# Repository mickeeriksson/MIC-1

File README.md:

# MIC-1
This is the repo for MIC-1

## Contents
- kernels/ : contains the MONITOR ROM source for MIC-1

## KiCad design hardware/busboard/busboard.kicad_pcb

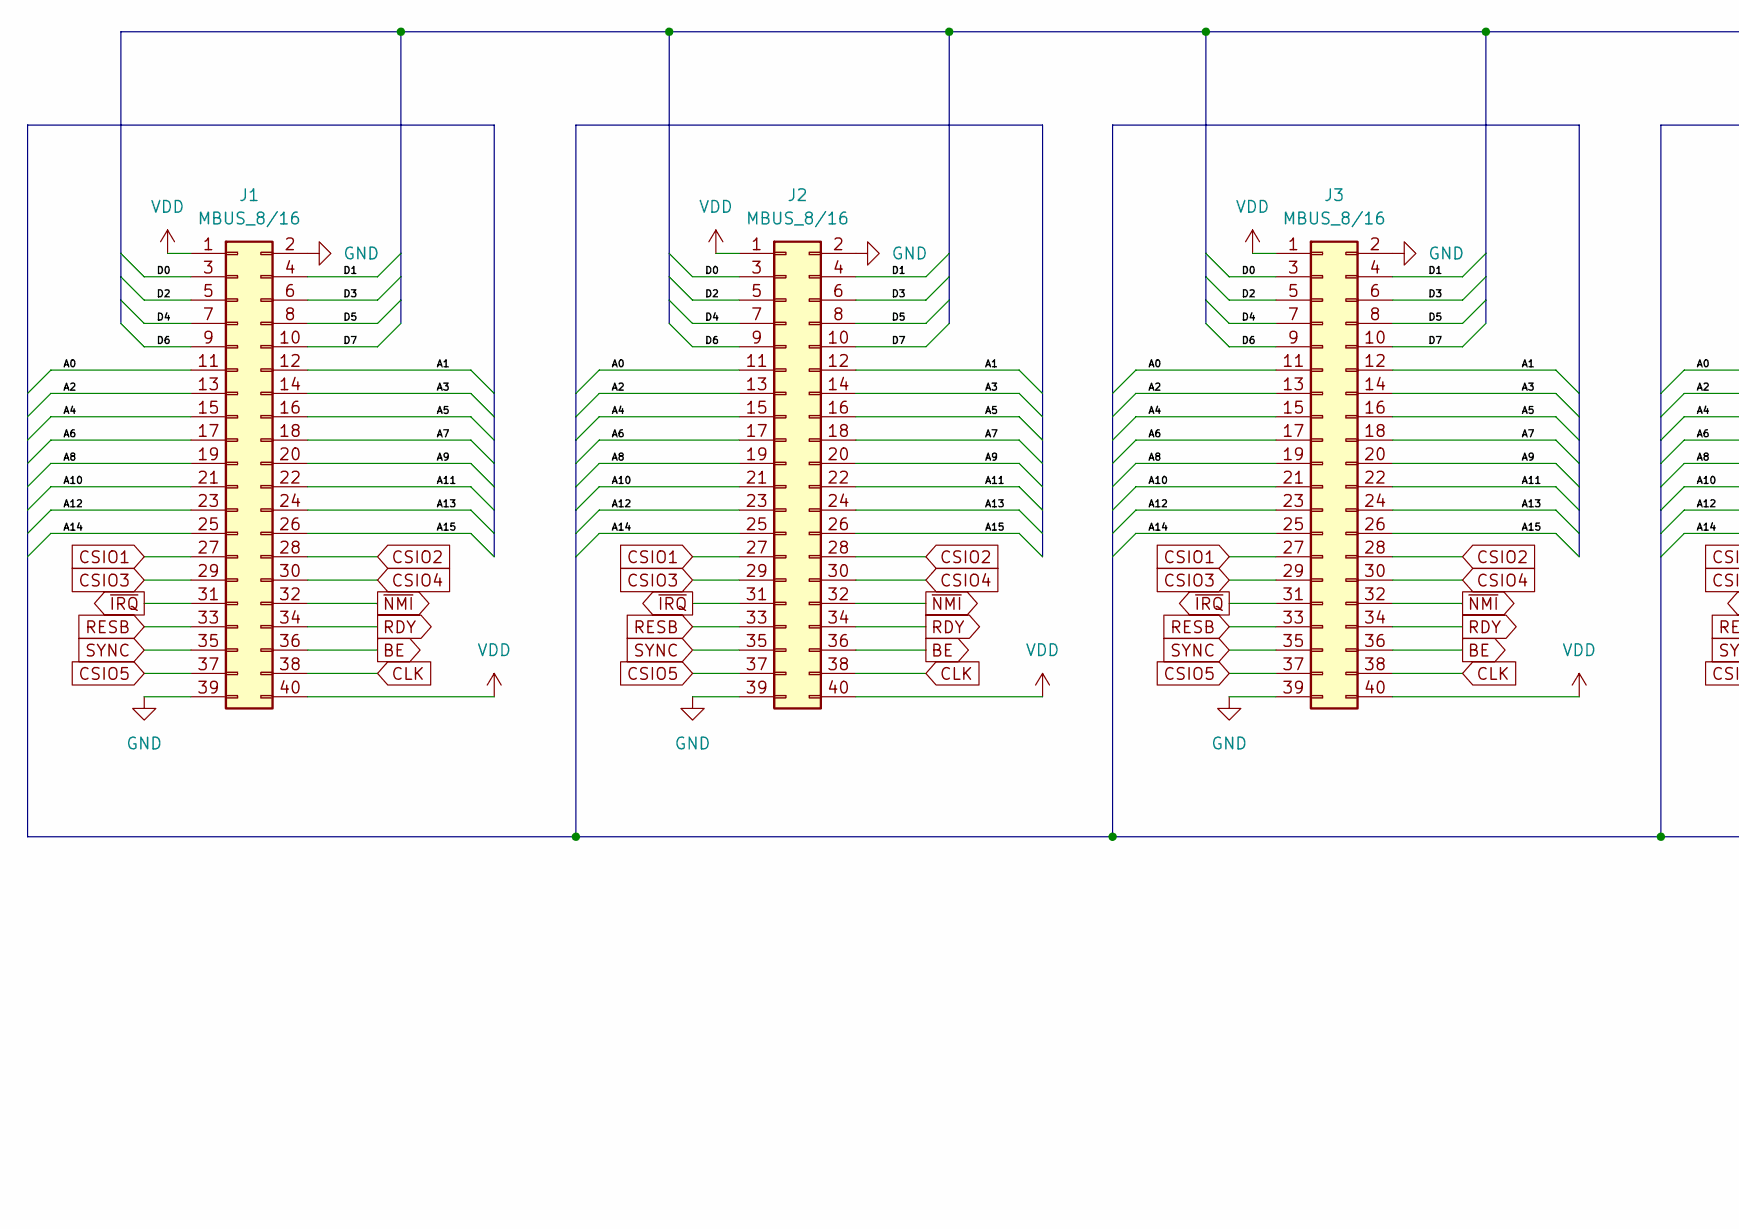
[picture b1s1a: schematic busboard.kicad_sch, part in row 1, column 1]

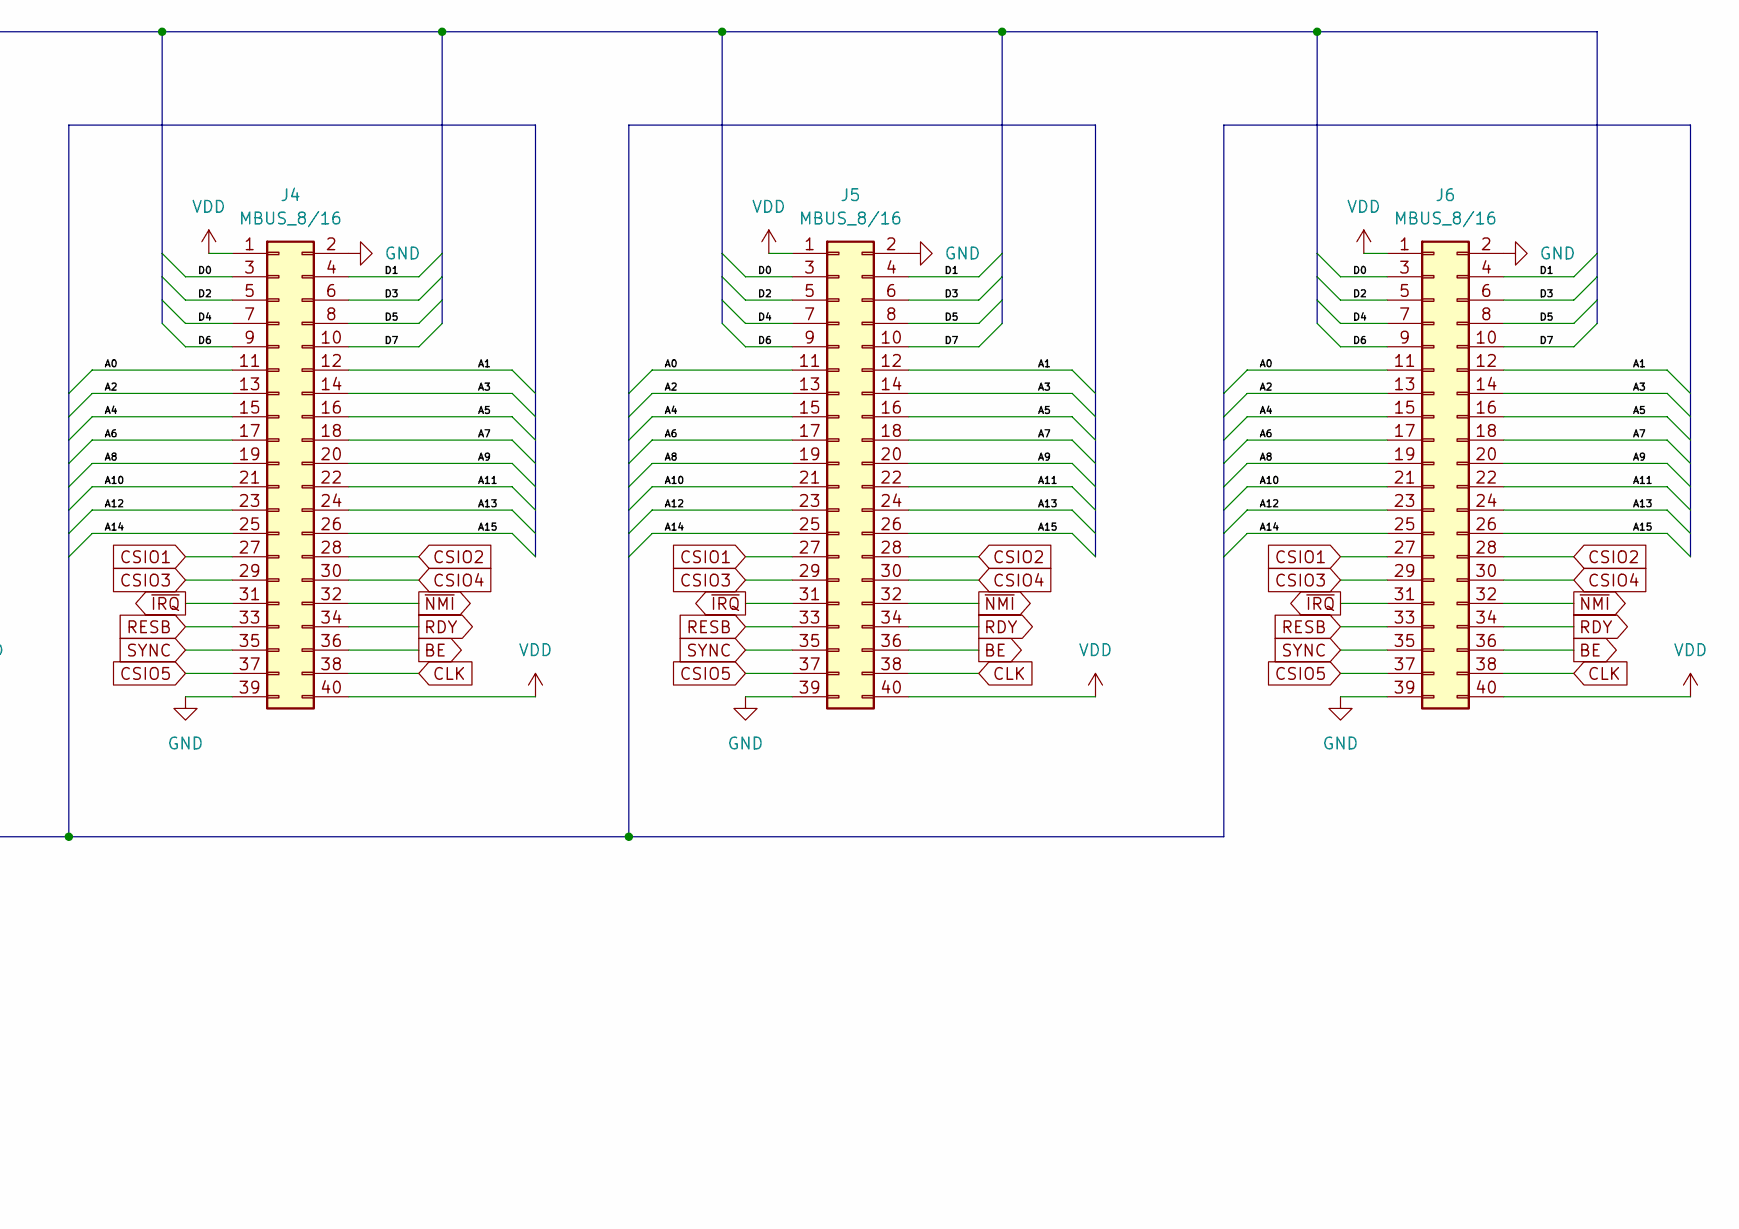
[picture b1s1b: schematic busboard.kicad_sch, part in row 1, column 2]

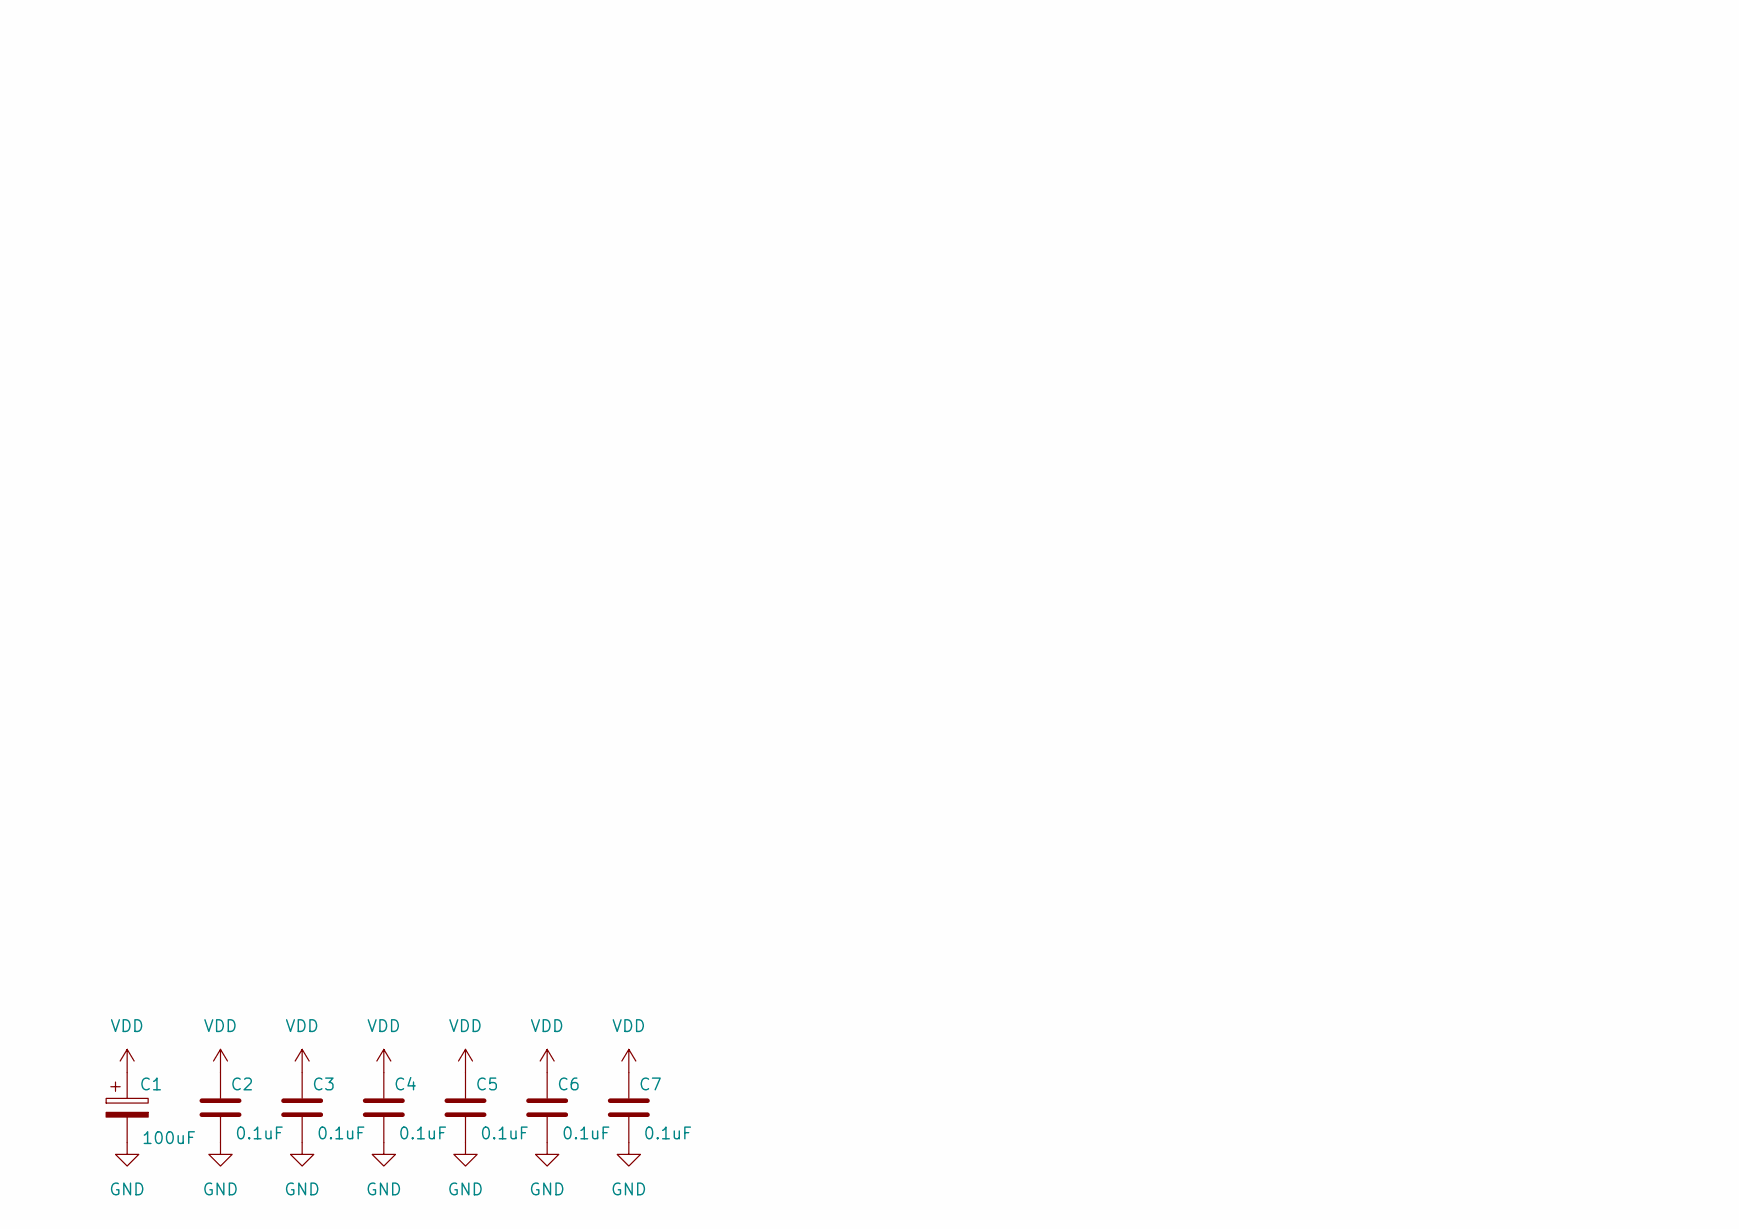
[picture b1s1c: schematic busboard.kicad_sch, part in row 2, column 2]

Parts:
C1: 100uF; CP_Radial_D5.0mm_P2.50mm
C2, C3, C4, C5, C6, C7: 0.1uF; C_Disc_D3.0mm_W2.0mm_P2.50mm
J1, J2, J3, J4, J5, J6: MBUS_8/16; PinHeader_2x20_P2.54mm_Vertical

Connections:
/A0: J1.11, J2.11, J3.11, J4.11, J5.11, J6.11
/A1: J1.12, J2.12, J3.12, J4.12, J5.12, J6.12
/A2: J1.13, J2.13, J3.13, J4.13, J5.13, J6.13
/A3: J1.14, J2.14, J3.14, J4.14, J5.14, J6.14
/A4: J1.15, J2.15, J3.15, J4.15, J5.15, J6.15
/A5: J1.16, J2.16, J3.16, J4.16, J5.16, J6.16
/A6: J1.17, J2.17, J3.17, J4.17, J5.17, J6.17
/A7: J1.18, J2.18, J3.18, J4.18, J5.18, J6.18
/A8: J1.19, J2.19, J3.19, J4.19, J5.19, J6.19
/A9: J1.20, J2.20, J3.20, J4.20, J5.20, J6.20
/A10: J1.21, J2.21, J3.21, J4.21, J5.21, J6.21
/A11: J1.22, J2.22, J3.22, J4.22, J5.22, J6.22
/A12: J1.23, J2.23, J3.23, J4.23, J5.23, J6.23
/A13: J1.24, J2.24, J3.24, J4.24, J5.24, J6.24
/A14: J1.25, J2.25, J3.25, J4.25, J5.25, J6.25
/A15: J1.26, J2.26, J3.26, J4.26, J5.26, J6.26
/D0: J1.3, J2.3, J3.3, J4.3, J5.3, J6.3
/D1: J1.4, J2.4, J3.4, J4.4, J5.4, J6.4
/D2: J1.5, J2.5, J3.5, J4.5, J5.5, J6.5
/D3: J1.6, J2.6, J3.6, J4.6, J5.6, J6.6
/D4: J1.7, J2.7, J3.7, J4.7, J5.7, J6.7
/D5: J1.8, J2.8, J3.8, J4.8, J5.8, J6.8
/D6: J1.9, J2.9, J3.9, J4.9, J5.9, J6.9
/D7: J1.10, J2.10, J3.10, J4.10, J5.10, J6.10
BE: J1.36, J2.36, J3.36, J4.36, J5.36, J6.36
CLK: J1.38, J2.38, J3.38, J4.38, J5.38, J6.38
CSIO1: J1.27, J2.27, J3.27, J4.27, J5.27, J6.27
CSIO2: J1.28, J2.28, J3.28, J4.28, J5.28, J6.28
CSIO3: J1.29, J2.29, J3.29, J4.29, J5.29, J6.29
CSIO4: J1.30, J2.30, J3.30, J4.30, J5.30, J6.30
CSIO5: J1.37, J2.37, J3.37, J4.37, J5.37, J6.37
GND: C1.2, C2.2, C3.2, C4.2, C5.2, C6.2, C7.2, J1.2, J1.39, J2.2, J2.39, J3.2, J3.39, J4.2, J4.39, J5.2, J5.39, J6.2, J6.39
RDY: J1.34, J2.34, J3.34, J4.34, J5.34, J6.34
RESB: J1.33, J2.33, J3.33, J4.33, J5.33, J6.33
SYNC: J1.35, J2.35, J3.35, J4.35, J5.35, J6.35
VDD: C1.1, C2.1, C3.1, C4.1, C5.1, C6.1, C7.1, J1.1, J1.40, J2.1, J2.40, J3.1, J3.40, J4.1, J4.40, J5.1, J5.40, J6.1, J6.40
~IRQ: J1.31, J2.31, J3.31, J4.31, J5.31, J6.31
~NMI: J1.32, J2.32, J3.32, J4.32, J5.32, J6.32

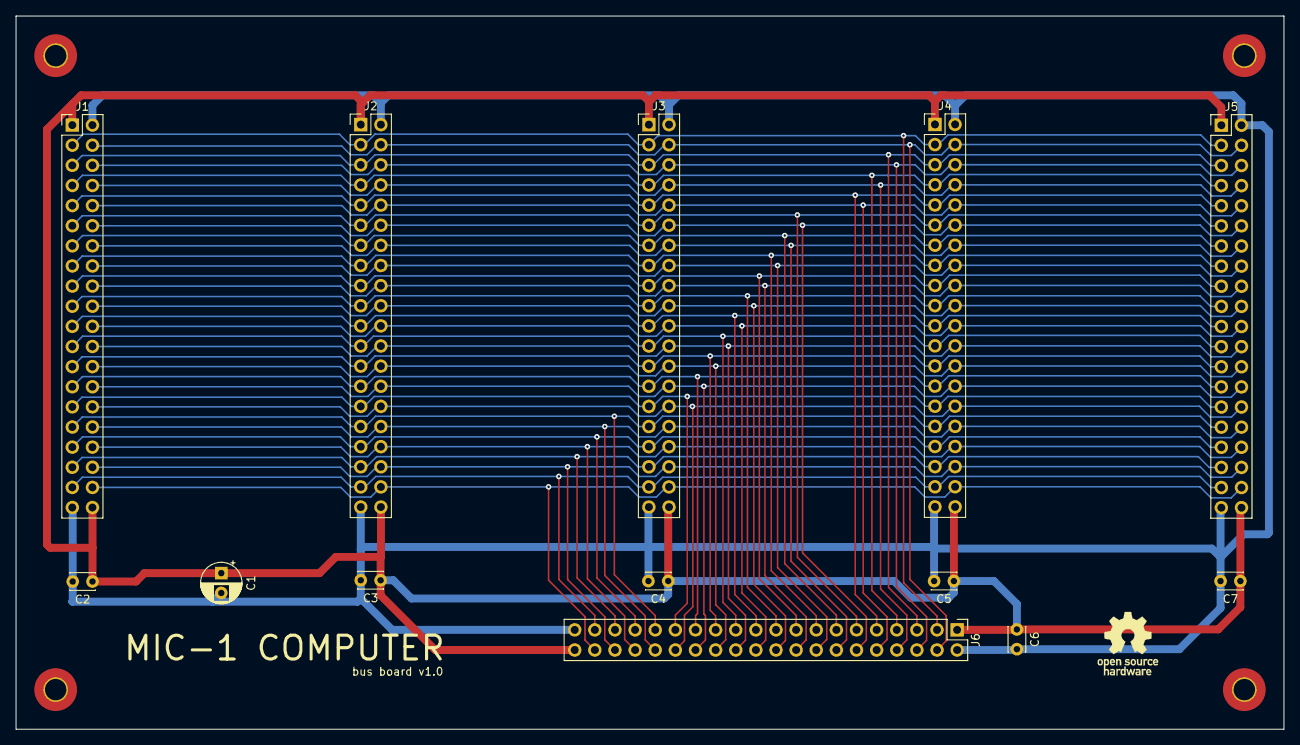
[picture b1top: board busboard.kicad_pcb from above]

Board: 2 copper layers, 160.0 x 90.0 mm, 17 parts (0 on the bottom side), 38 nets.

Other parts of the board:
hole1, hole1#2, hole1#3, hole1#4: MountingHole_2.7mm_M2.5_Pad_TopBottom

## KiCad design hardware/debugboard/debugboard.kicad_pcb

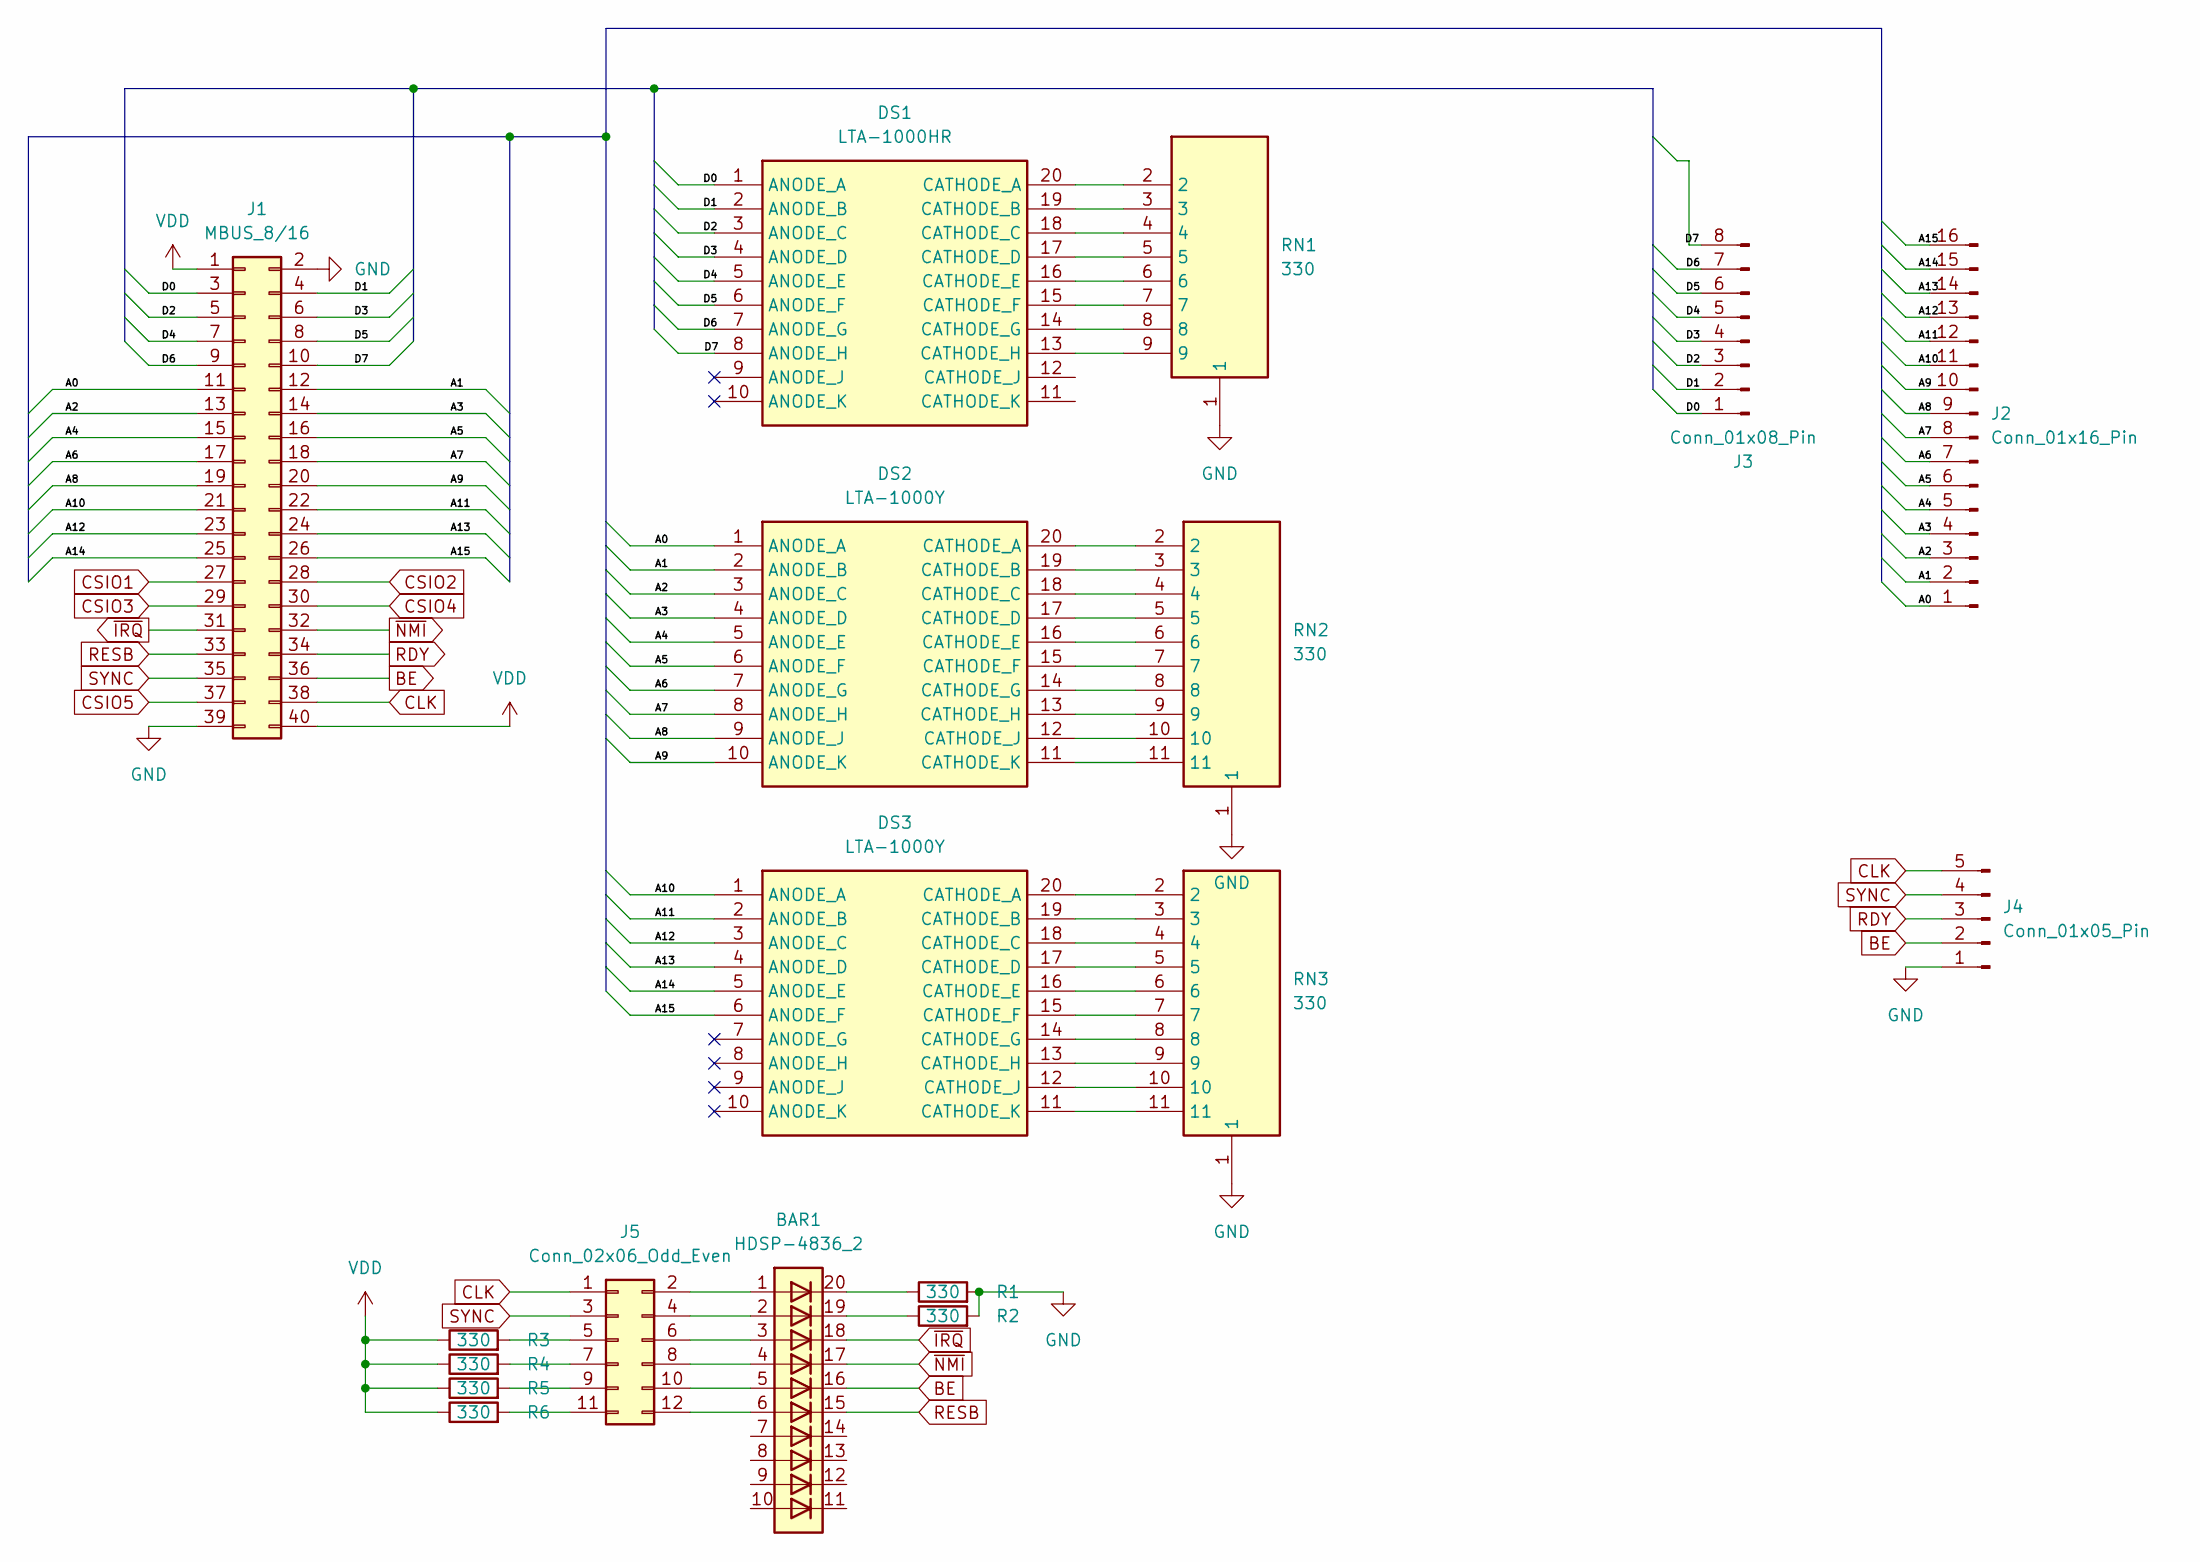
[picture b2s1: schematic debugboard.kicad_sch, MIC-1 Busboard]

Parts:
BAR1: HDSP-4836_2; HDSP-4836
DS1: LTA-1000HR; DIPS762W50P254L2527H825Q20N; Mouser Part Number 859-LTA-1000HR
DS2, DS3: LTA-1000Y; DIPS762W50P254L2527H825Q20N; Mouser Part Number 859-LTA-1000Y
J1: MBUS_8/16; PinHeader_2x20_P2.54mm_Vertical
J2: Conn_01x16_Pin; PinHeader_1x16_P2.54mm_Vertical
J3: Conn_01x08_Pin; PinHeader_1x08_P2.54mm_Vertical
J4: Conn_01x05_Pin; PinHeader_1x05_P2.54mm_Vertical
J5: Conn_02x06_Odd_Even; PinHeader_2x06_P2.54mm_Vertical
R1, R2, R3, R4, R5, R6: 330; R_Axial_DIN0207_L6.3mm_D2.5mm_P7.62mm_Horizontal
RN1: 330; 4609X101102LF; Manufacturer_Part_Number 4609X-101-331LF
RN2, RN3: 330; 4611X101221LF; Manufacturer_Part_Number 4611X-101-331LF

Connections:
/A0: DS2.1 (ANODE_A), J1.11, J2.1
/A1: DS2.2 (ANODE_B), J1.12, J2.2
/A2: DS2.3 (ANODE_C), J1.13, J2.3
/A3: DS2.4 (ANODE_D), J1.14, J2.4
/A4: DS2.5 (ANODE_E), J1.15, J2.5
/A5: DS2.6 (ANODE_F), J1.16, J2.6
/A6: DS2.7 (ANODE_G), J1.17, J2.7
/A7: DS2.8 (ANODE_H), J1.18, J2.8
/A8: DS2.9 (ANODE_J), J1.19, J2.9
/A9: DS2.10 (ANODE_K), J1.20, J2.10
/A10: DS3.1 (ANODE_A), J1.21, J2.11
/A11: DS3.2 (ANODE_B), J1.22, J2.12
/A12: DS3.3 (ANODE_C), J1.23, J2.13
/A13: DS3.4 (ANODE_D), J1.24, J2.14
/A14: DS3.5 (ANODE_E), J1.25, J2.15
/A15: DS3.6 (ANODE_F), J1.26, J2.16
/D0: DS1.1 (ANODE_A), J1.3, J3.1
/D1: DS1.2 (ANODE_B), J1.4, J3.2
/D2: DS1.3 (ANODE_C), J1.5, J3.3
/D3: DS1.4 (ANODE_D), J1.6, J3.4
/D4: DS1.5 (ANODE_E), J1.7, J3.5
/D5: DS1.6 (ANODE_F), J1.8, J3.6
/D6: DS1.7 (ANODE_G), J1.9, J3.7
/D7: DS1.8 (ANODE_H), J1.10, J3.8
BE: BAR1.16 (K), J1.36, J4.2
CLK: J1.38, J4.5, J5.1
CSIO1: J1.27
CSIO2: J1.28
CSIO3: J1.29
CSIO4: J1.30
CSIO5: J1.37
GND: J1.2, J1.39, J4.1, R1.2, R2.2, RN1.1, RN2.1, RN3.1
unnamed: BAR1.19 (K), R2.1
unnamed: BAR1.20 (K), R1.1
unnamed: DS1.20 (CATHODE_A), RN1.2
unnamed: DS1.19 (CATHODE_B), RN1.3
unnamed: DS1.18 (CATHODE_C), RN1.4
unnamed: DS1.17 (CATHODE_D), RN1.5
unnamed: DS1.16 (CATHODE_E), RN1.6
unnamed: DS1.15 (CATHODE_F), RN1.7
unnamed: DS1.14 (CATHODE_G), RN1.8
unnamed: DS1.13 (CATHODE_H), RN1.9
unnamed: DS2.20 (CATHODE_A), RN2.2
unnamed: DS2.19 (CATHODE_B), RN2.3
unnamed: DS2.18 (CATHODE_C), RN2.4
unnamed: DS2.17 (CATHODE_D), RN2.5
unnamed: DS2.16 (CATHODE_E), RN2.6
unnamed: DS2.15 (CATHODE_F), RN2.7
unnamed: DS2.14 (CATHODE_G), RN2.8
unnamed: DS2.13 (CATHODE_H), RN2.9
unnamed: DS2.12 (CATHODE_J), RN2.10
unnamed: DS2.11 (CATHODE_K), RN2.11
unnamed: DS3.20 (CATHODE_A), RN3.2
unnamed: DS3.19 (CATHODE_B), RN3.3
unnamed: DS3.18 (CATHODE_C), RN3.4
unnamed: DS3.17 (CATHODE_D), RN3.5
unnamed: DS3.16 (CATHODE_E), RN3.6
unnamed: DS3.15 (CATHODE_F), RN3.7
unnamed: DS3.14 (CATHODE_G), RN3.8
unnamed: DS3.13 (CATHODE_H), RN3.9
unnamed: DS3.12 (CATHODE_J), RN3.10
unnamed: DS3.11 (CATHODE_K), RN3.11
unnamed: BAR1.1 (A), J5.2
unnamed: BAR1.2 (A), J5.4
unnamed: J5.5, R3.2
unnamed: BAR1.3 (A), J5.6
unnamed: J5.7, R4.2
unnamed: BAR1.4 (A), J5.8
unnamed: J5.9, R5.2
unnamed: BAR1.5 (A), J5.10
unnamed: J5.11, R6.2
unnamed: BAR1.6 (A), J5.12
RDY: J1.34, J4.3
RESB: BAR1.15 (K), J1.33
SYNC: J1.35, J4.4, J5.3
VDD: J1.1, J1.40, R3.1, R4.1, R5.1, R6.1
~IRQ: BAR1.18 (K), J1.31
~NMI: BAR1.17 (K), J1.32

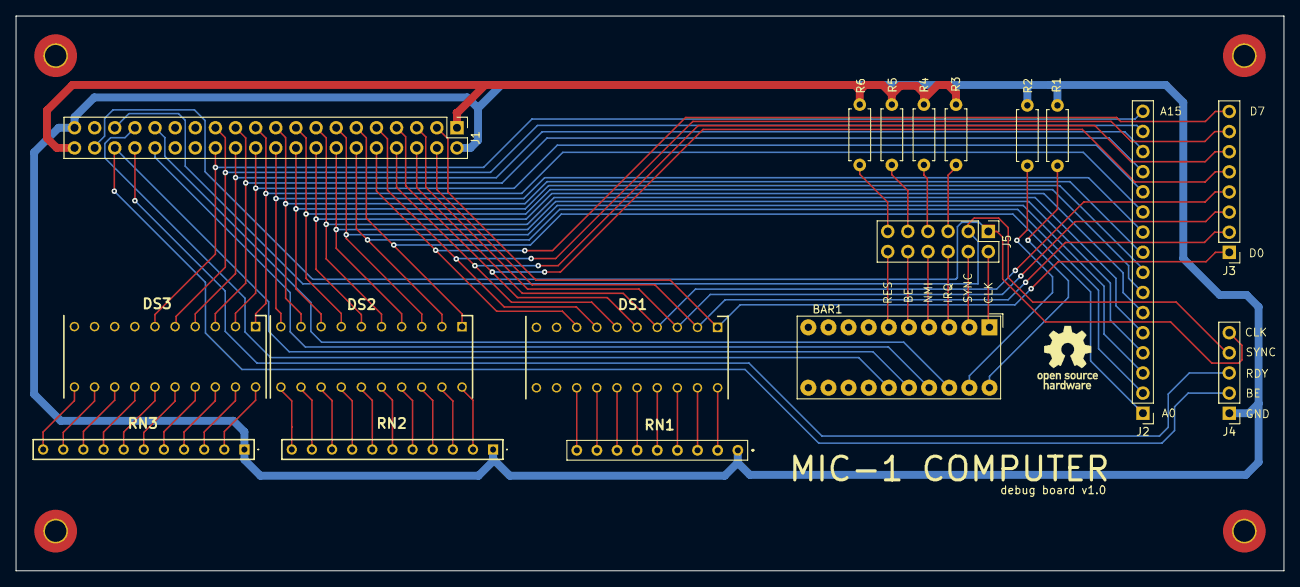
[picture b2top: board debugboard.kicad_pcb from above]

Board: 2 copper layers, 160.0 x 70.0 mm, 22 parts (0 on the bottom side), 73 nets.

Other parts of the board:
hole1, hole1#2, hole1#3, hole1#4: MountingHole_2.7mm_M2.5_Pad_TopBottom
